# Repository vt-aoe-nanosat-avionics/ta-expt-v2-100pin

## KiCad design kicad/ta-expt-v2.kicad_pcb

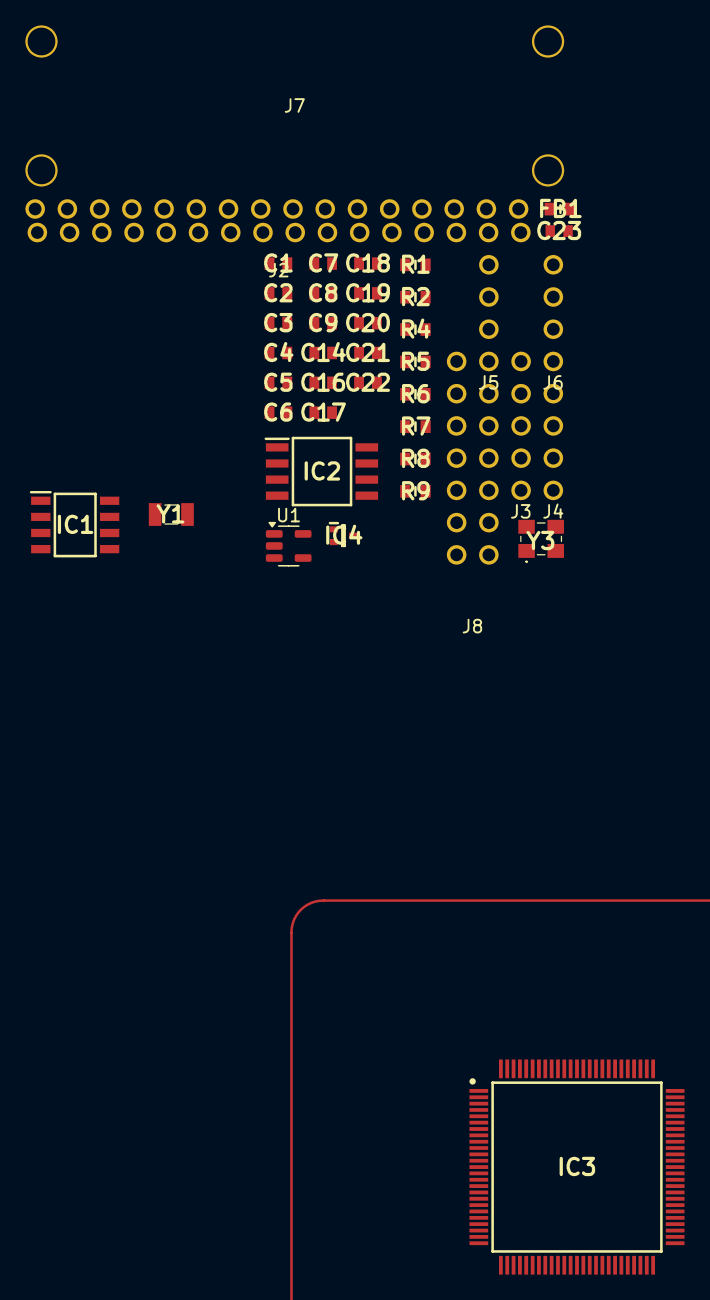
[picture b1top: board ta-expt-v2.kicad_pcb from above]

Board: 4 copper layers, 42 parts (0 on the bottom side), 43 nets, no tracks yet.

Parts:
C1: GRM188C71A475KE21D; CAPC1608X90N
C2, C3: 0603ZC105JAT2A; CAPC1608X90N
C4, C5, C14, C18, C19, C20, C21, C22: 0603ZC104JAT2A; CAPC1608X90N
C6, C7, C8, C9: 0603ZA220JAT2A; CAPC1608X90N
C16, C17: 1uF; CAPC1608X90N
C23: GRM1857U1A103JA44D; CAPC1608X50N
FB1: MMZ1608S601ATD25; BEADC1608X95N
IC1: STS5PF30L; SOIC127P600X175-8N
IC2: IS25LP128F-JBLA3; SOIC127P790X216-8N
IC3: STM32L496VGT3; QFP50P1600X1600X160-100N
IC4: BAR43SFILM; SOTFL50P160X78-3N
J1, J2: Conn_01x16; PinSocket_1x16_TartanArtibeus
J3, J4: Conn_01x04; PinSocket_4x1_TartanArtibeus
J5, J6: Conn_01x05; PinSocket_1x5_TartanArtibeus
J7: Conn_01x04; MountingHoles_TartanArtibeus
J8: Conn_02x06_Odd_Even; PinSocket_6x2_TartanArtibeus
R1, R2, R8: MCT06030C1001FP500; RESC1608X55N
R4, R5, R9: MCT06030C1002FP500; RESC1608X55N
R6, R7: 5.1k; RESC1608X55N
U1: TPS7A0533PDBV; SOT-23-5
Y1: ABS07AIG-32.768kHz-T; ABS07AIG32768kHz71T
Y3: ABM8AIG-16.000MHZ-12-2Z-T; ABM8AIG25000MHZ122ZT3

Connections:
/BOOT0: J2.8, R8.1
/Control: IC3.4 (PE5), R4.1
/DCMI_D0: IC3.63 (PC6), J8.1
/DCMI_D1: IC3.64 (PC7), J8.2
/DCMI_D2: IC3.65 (PC8), J8.3
/DCMI_D3: IC3.66 (PC9), J8.4
/DCMI_D4: IC3.79 (PC11), J8.5
/DCMI_D5: IC3.92 (PB6), J8.6
/DCMI_D6: IC3.95 (PB8), J8.7
/DCMI_D7: IC3.96 (PB9), J8.8
/DCMI_HSYNC: IC3.29 (PA4), J8.11
/DCMI_PIXCLK: IC3.31 (PA6), J8.10
/DCMI_VSYNC: IC3.93 (PB7), J8.12
/LDO_OUT: C17.1, IC1.5 (D_1), IC1.6 (D_2), IC1.7 (D_3), IC1.8 (D_4), IC3.5 (PE6), U1.5 (OUT)
/LED1: IC3.78 (PC10), R1.1
/LED2: IC3.80 (PC12), R2.1
/LPUART_CTS: IC3.52 (PB13), J2.9
/LPUART_RTS: IC3.51 (PB12), J2.12
/LPUART_RX: IC3.47 (PB10), J2.11
/LPUART_TX: IC3.48 (PB11), J2.10
/NRST: C5.1, IC3.14 (NRST), J1.7
/QUADSPI_BK1_NCS: IC2.1 (CE#), IC3.25 (PA2), R5.2
/QUADSPI_BK2_IO0: IC2.5 (SI(IO0)), IC3.16 (PC1)
/QUADSPI_BK2_IO1: IC2.2 (SO(IO1)), IC3.17 (PC2)
/QUADSPI_BK2_IO2: IC2.3 (WP#(IO2)), IC3.18 (PC3)
/QUADSPI_BK2_IO3: IC2.7 (HOLD#_OR__RESET#(IO3)), IC3.33 (PC4)
/QUADSPI_CLK: IC2.6 (SCK), IC3.26 (PA3)
/SWCLK: IC3.76 (PA14), J4.4
/SWDIO: IC3.72 (PA13), J4.3
/USART1_CK: IC3.67 (PA8), J1.8
/USART1_RX: IC3.69 (PA10), J1.11
/USART1_TX: IC3.68 (PA9), J1.10
/VBUS: C16.2, U1.1 (IN), U1.3 (EN)
/VDD_FILT: C1.1, C2.1, C3.1, C4.1, C14.1, C18.1, C19.2, C20.2, C21.2, C22.2, C23.1, FB1.2, IC1.1 (S_1), IC1.2 (S_2), IC1.3 (S_3), IC2.8 (VCC), IC3.11 (VDD_1), IC3.21 (VREF+), IC3.22 (VDDA), IC3.28 (VDD_2), IC3.50 (VDD_3), IC3.73 (VDDUSB), IC3.75 (VDD_4), IC3.100 (VDD_5), R5.1
/V_BAT: IC3.6 (VBAT), IC4.1 (A2)
GND: C1.2, C2.2, C3.2, C4.2, C5.2, C6.2, C7.2, C8.2, C9.2, C14.2, C16.1, C17.2, C18.2, C19.1, C20.1, C21.1, C22.1, C23.2, IC2.4 (GND), IC3.10 (VSS_1), IC3.19 (VSSA), IC3.20 (VREF-), IC3.27 (VSS_2), IC3.49 (VSS_3), IC3.74 (VSS_4), IC3.99 (VSS_5), J1.3, J3.2, J4.2, J6.3, J7.1, J7.2, J7.3, J7.4, R6.1, R7.1, R9.2, U1.2 (GND), Y3.2 (GND_1), Y3.4 (GND_2)
unnamed: IC1.4 (G), R4.2
unnamed: C8.1, IC3.8 (PC14-OSC32_IN), Y1.1
unnamed: C9.1, IC3.9 (PC15-OSC32_OUT), Y1.2
unnamed: C6.1, IC3.12 (PH0-OSC_IN), Y3.1 (CRYSTAL_1)
unnamed: C7.1, IC3.13 (PH1-OSC_OUT), Y3.3 (CRYSTAL_2)
unnamed: IC3.94 (PH3-BOOT0), R8.2, R9.1
VDD: FB1.1, J4.1

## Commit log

2024-10-18 Add files via upload
    Adding new information to repository
